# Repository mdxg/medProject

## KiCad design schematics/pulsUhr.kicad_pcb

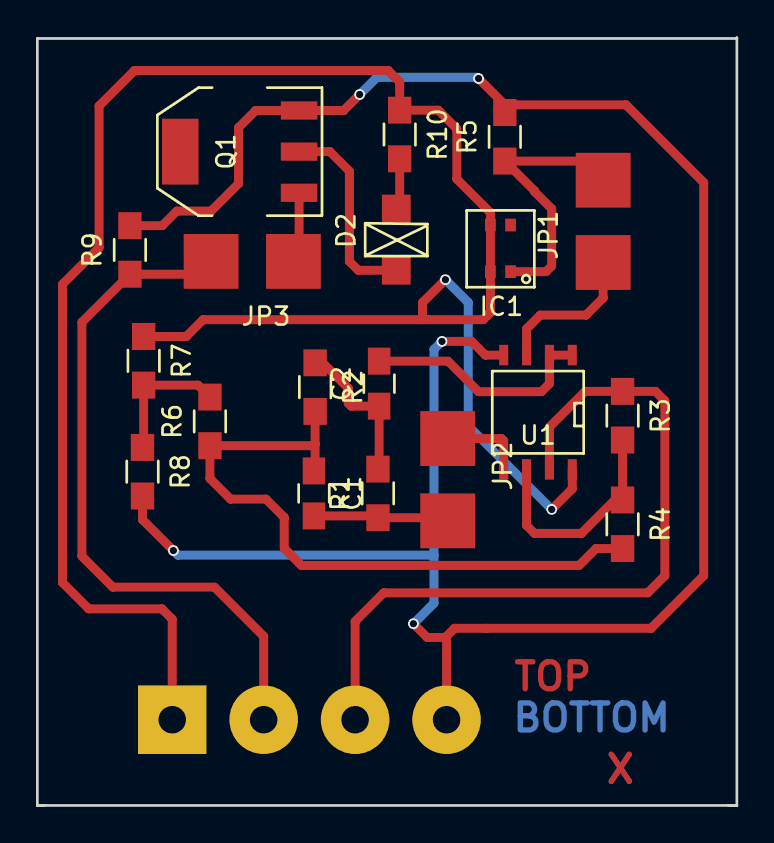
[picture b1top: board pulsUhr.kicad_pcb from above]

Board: 2 copper layers, 38.9 x 42.7 mm, 20 parts (1 on the bottom side), 16 nets.

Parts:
C1: 82nF; C_0805_HandSoldering
C2: 3,3nF; C_0805_HandSoldering
D2: LED; SMD_REVERSE_MOUNT
IC1: APDS-9006-020; APDS-9006-0200
JP1, JP2, JP3: Jumper_NC_Small; SOLDER_JUMPER
P1: CONN_01X04; bornier4
Q1: ZVN2106G; SOT-223
R1, R2: 10M; R_0805_HandSoldering
R3: 2K8; R_0805_HandSoldering
R4: 200; R_0805_HandSoldering
R5: 1K; R_0805_HandSoldering
R6: 100K; R_0805_HandSoldering
R7, R8: 10K; R_0805_HandSoldering
R9: 100k; R_0805_HandSoldering
R10: 150; R_0805_HandSoldering
U1: MCP6002; SOIC-8-N

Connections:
+5V: IC1.2, IC1.3, P1.1, R7.1, R10.1, U1.8
GND: P1.4, Q1.3, R5.2, R8.2, R9.2, U1.4
LED: JP3.1, P1.2, R9.1
unnamed: C1.2, JP2.1, R1.1
unnamed: C2.1, R1.2, R2.1
unnamed: C2.2, U1.1, U1.2
unnamed: D2.1, Q1.2
unnamed: D2.2, R10.2
unnamed: IC1.1, JP1.1, R5.1
unnamed: JP1.2, U1.3
unnamed: JP2.2, U1.5
unnamed: JP3.2, Q1.1
unnamed: R3.2, R4.1, U1.6
unnamed: R6.2, R7.2, R8.1
OUT: P1.3, R3.1, U1.7
VGND: C1.1, R2.2, R4.2, R6.1

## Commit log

2016-04-22 Start kicad project
2016-04-25 Telegram Bot Test
2016-05-06 Initial Android commit
2016-05-25 first hardware version
2016-05-27 Added Bluetooth Functions
2016-06-03 New Layout for version 0.1
2016-06-15 such Commit, Much Bluetooth fix
2016-06-16 created new Layout files for all screens using fragments
2016-06-20 much commit
2016-06-20 much commit2
2016-06-20 added mc prog
2016-06-20 clean
2016-06-20 new mc prog
